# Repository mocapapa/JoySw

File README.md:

# JoySw
Joystick and Switch Interface

- JOYSW.brd ---- EAGLE layout data
- JOYSW.sch ---- EAGLE schematic data
- JOYSW_2019-01-09.zip --- Gerber data
- JOYSW.csv ---- BOM file

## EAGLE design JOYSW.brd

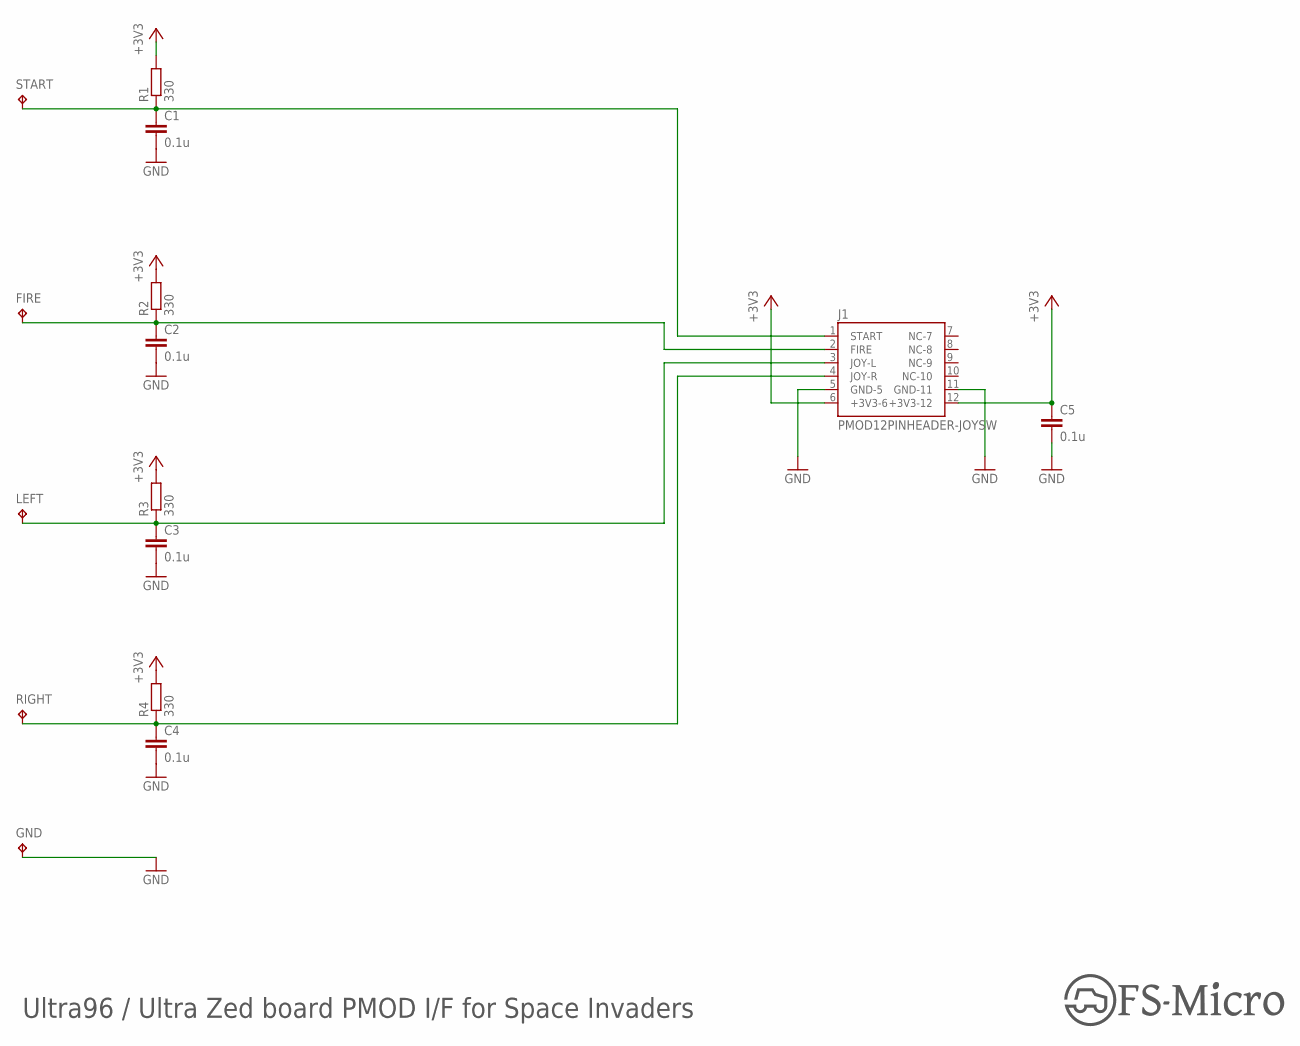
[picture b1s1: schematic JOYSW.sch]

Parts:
C1, C2, C3, C4, C5: 0.1u; C050-025X075
FIRE: TPPAD1-13; P1-13
GND: TPPAD1-13; P1-13
J1: PMOD12PINHEADER-JOYSW; PMOD12PINHEADER
LEFT: TPPAD1-13; P1-13
R1, R2, R3, R4: 330; 0207/7
RIGHT: TPPAD1-13; P1-13
START: TPPAD1-13; P1-13

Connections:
+3V3: C5.1, J1.6 (+3V3-6), J1.12 (+3V3-12), R1.2, R2.2, R3.2, R4.2
FIRE: C2.1, FIRE.TP, J1.2 (FIRE), R2.1
GND: C1.2, C2.2, C3.2, C4.2, C5.2, GND.TP, J1.5 (GND-5), J1.11 (GND-11)
JOY-L: C3.1, J1.3 (JOY-L), LEFT.TP, R3.1
JOY-R: C4.1, J1.4 (JOY-R), R4.1, RIGHT.TP
START: C1.1, J1.1 (START), R1.1, START.TP

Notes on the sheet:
Ultra96 / Ultra Zed board PMOD I/F for Space Invaders

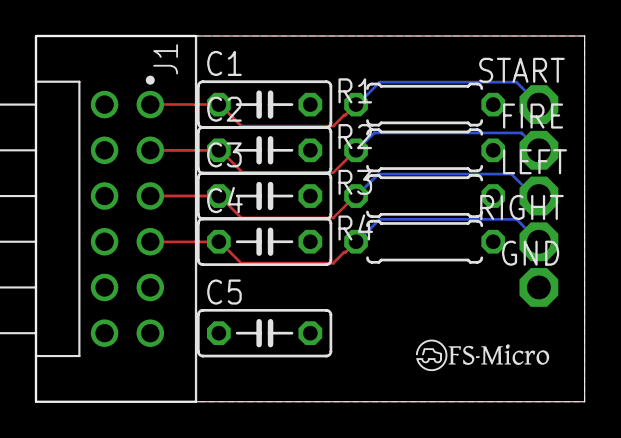
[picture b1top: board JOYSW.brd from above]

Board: 2 copper layers, 30.5 x 20.3 mm, 15 parts (0 on the bottom side), 6 nets.
